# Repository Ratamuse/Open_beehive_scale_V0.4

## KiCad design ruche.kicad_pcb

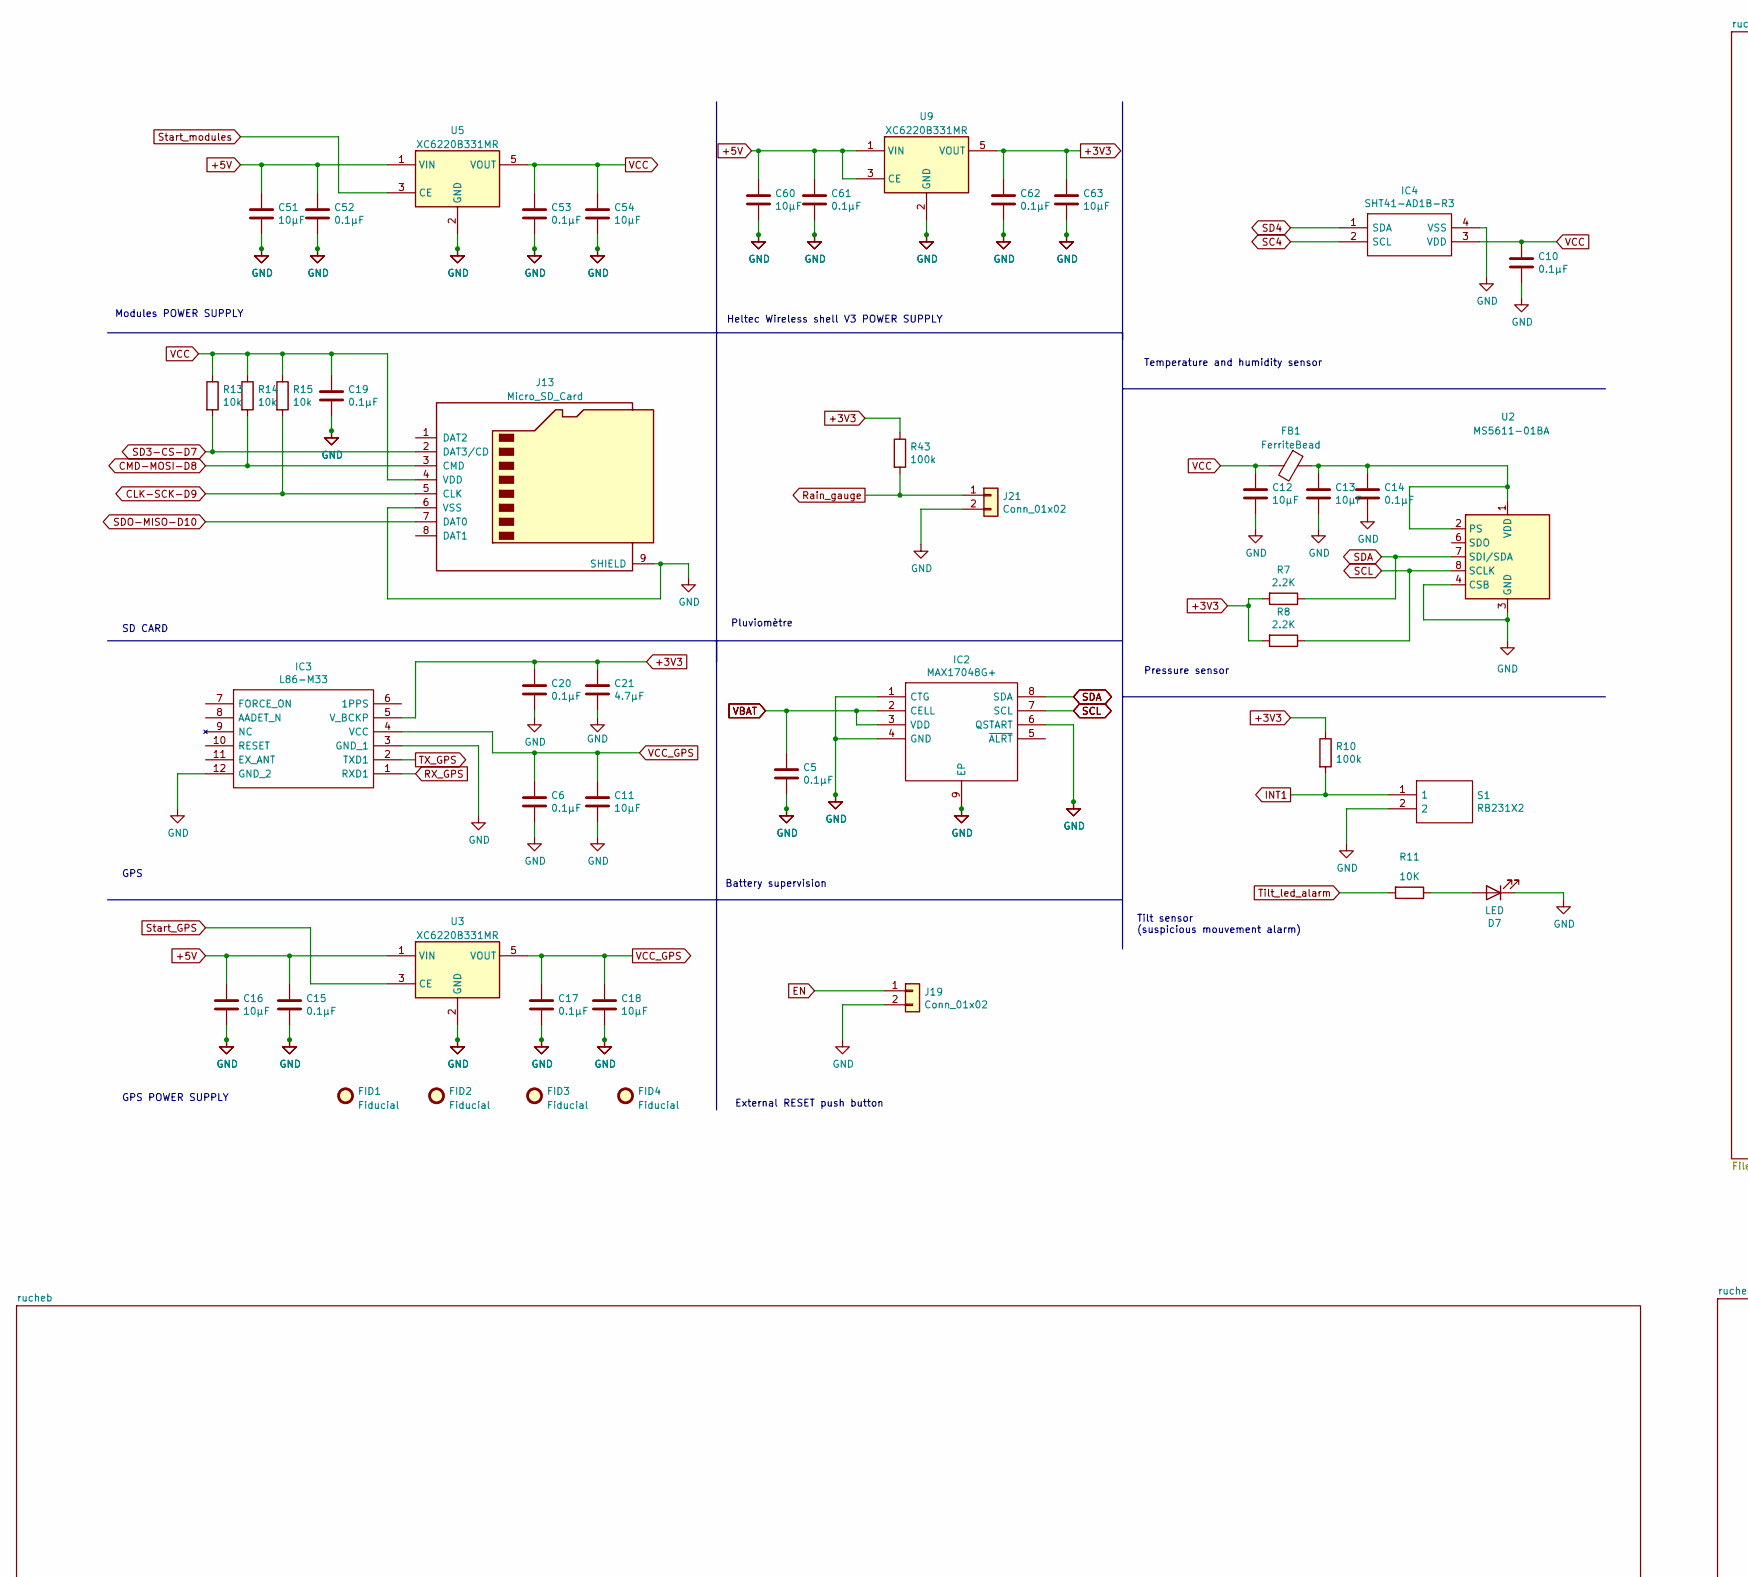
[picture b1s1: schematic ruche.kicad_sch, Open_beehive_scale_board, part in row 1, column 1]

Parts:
C5, C6, C10, C14, C17, C19, C20, C52, C53, C61, C62: 0.1µF; C_0603_1608Metric
C11, C12, C13, C18, C51, C54, C60, C63: 10µF; C_0805_2012Metric
C15: 0.1µF; C_0805_2012Metric
C16: 10µF; C_0603_1608Metric
C21: 4.7µF; C_0805_2012Metric
D7: LED; LED_0603_1608Metric
FB1: FerriteBead; R_0603_1608Metric
FID1, FID2, FID3, FID4: Fiducial; Fiducial_1mm_Mask3mm
IC2: MAX17048G+; SON50P200X200X80-9N-D; Manufacturer_Part_Number MAX17048G+; Mouser Part Number 700-MAX17048G+
IC3: L86-M33; L80-M39; Manufacturer_Part_Number L86-M33
IC4: SHT41-AD1B-R3; SHT41AD1BR3; Manufacturer_Part_Number SHT41-AD1B-R3; Mouser Part Number 403-SHT41-AD1B-R3
J13: Micro_SD_Card; microSD_HC_Hirose_DM3AT-SF-PEJM5
J19, J21: Conn_01x02; JST_PH_B2B-PH-K_1x02_P2.00mm_Vertical
R7, R8: 2.2K; R_0603_1608Metric
R10, R43: 100k; R_0603_1608Metric
R11: 10K; R_0603_1608Metric
R13, R14, R15: 10k; R_0603_1608Metric
S1: RB231X2; Manufacturer_Part_Number RB231X2; Mouser Part Number 611-RB-231X2
U2: MS5611-01BA; LGA-8_3x5mm_P1.25mm
U3, U5, U9: XC6220B331MR; SOT-23-5

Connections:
+3V3: C20.1, C21.1, C62.1, C63.1, IC3.5 (V_BCKP), R7.2, R8.2, R10.1, R43.1, U9.5 (VOUT); also elsewhere on the board
+5V: C15.1, C16.1, C51.1, C52.1, C60.1, C61.1, U3.1 (VIN), U5.1 (VIN), U9.1 (VIN), U9.3 (CE); also elsewhere on the board
CLK-SCK-D9: J13.5 (CLK), R15.2; also elsewhere on the board
CMD-MOSI-D8: J13.3 (CMD), R14.2; also elsewhere on the board
EN: J19.1; also elsewhere on the board
GND: C5.2, C6.2, C10.2, C11.2, C12.2, C13.2, C14.2, C15.2, C16.2, C17.2, C18.2, C19.2, C20.2, C21.2, C51.2, C52.2, C53.2, C54.2, C60.2, C61.2, C62.2, C63.2, D7.1 (K), IC2.1 (CTG), IC2.4 (GND), IC2.6 (QSTART), IC2.9 (EP), IC3.3 (GND_1), IC3.12 (GND_2), IC4.4 (VSS), J13.6 (VSS), J13.9 (SHIELD), J19.2, J21.2, S1.2, U2.3 (GND), U2.4 (CSB), U2.5 (CSB), U3.2 (GND), U5.2 (GND), U9.2 (GND); also elsewhere on the board
INT1: R10.2, S1.1; also elsewhere on the board
unnamed: C13.1, C14.1, FB1.1, U2.1 (VDD), U2.2 (PS)
unnamed: D7.2 (A), R11.1
RX_GPS: IC3.1 (RXD1); also elsewhere on the board
Rain_gauge: J21.1, R43.2; also elsewhere on the board
SC4: IC4.2 (SCL); also elsewhere on the board
SCL: IC2.7 (SCL), R8.1, U2.8 (SCLK); also elsewhere on the board
SD3-CS-D7: J13.2 (DAT3/CD), R13.2; also elsewhere on the board
SD4: IC4.1 (SDA); also elsewhere on the board
SDA: IC2.8 (SDA), R7.1, U2.7 (SDI/SDA); also elsewhere on the board
SDO-MISO-D10: J13.7 (DAT0); also elsewhere on the board
Start_GPS: U3.3 (CE); also elsewhere on the board
Start_modules: U5.3 (CE); also elsewhere on the board
TX_GPS: IC3.2 (TXD1); also elsewhere on the board
Tilt_led_alarm: R11.2; also elsewhere on the board
VBAT: C5.1, IC2.2 (CELL), IC2.3 (VDD); also elsewhere on the board
VCC: C10.1, C12.1, C19.1, C53.1, C54.1, FB1.2, IC4.3 (VDD), J13.4 (VDD), R13.1, R14.1, R15.1, U5.5 (VOUT); also elsewhere on the board
VCC_GPS: C6.1, C11.1, C17.1, C18.1, IC3.4 (VCC), U3.5 (VOUT)

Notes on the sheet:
SD CARD
Pluviomètre
GPS
Battery supervision
Heltec Wireless shell V3 POWER SUPPLY
Tilt sensor (suspicious mouvement alarm)
Temperature and humidity sensor
External RESET push button
Pressure sensor
Modules POWER SUPPLY
GPS POWER SUPPLY

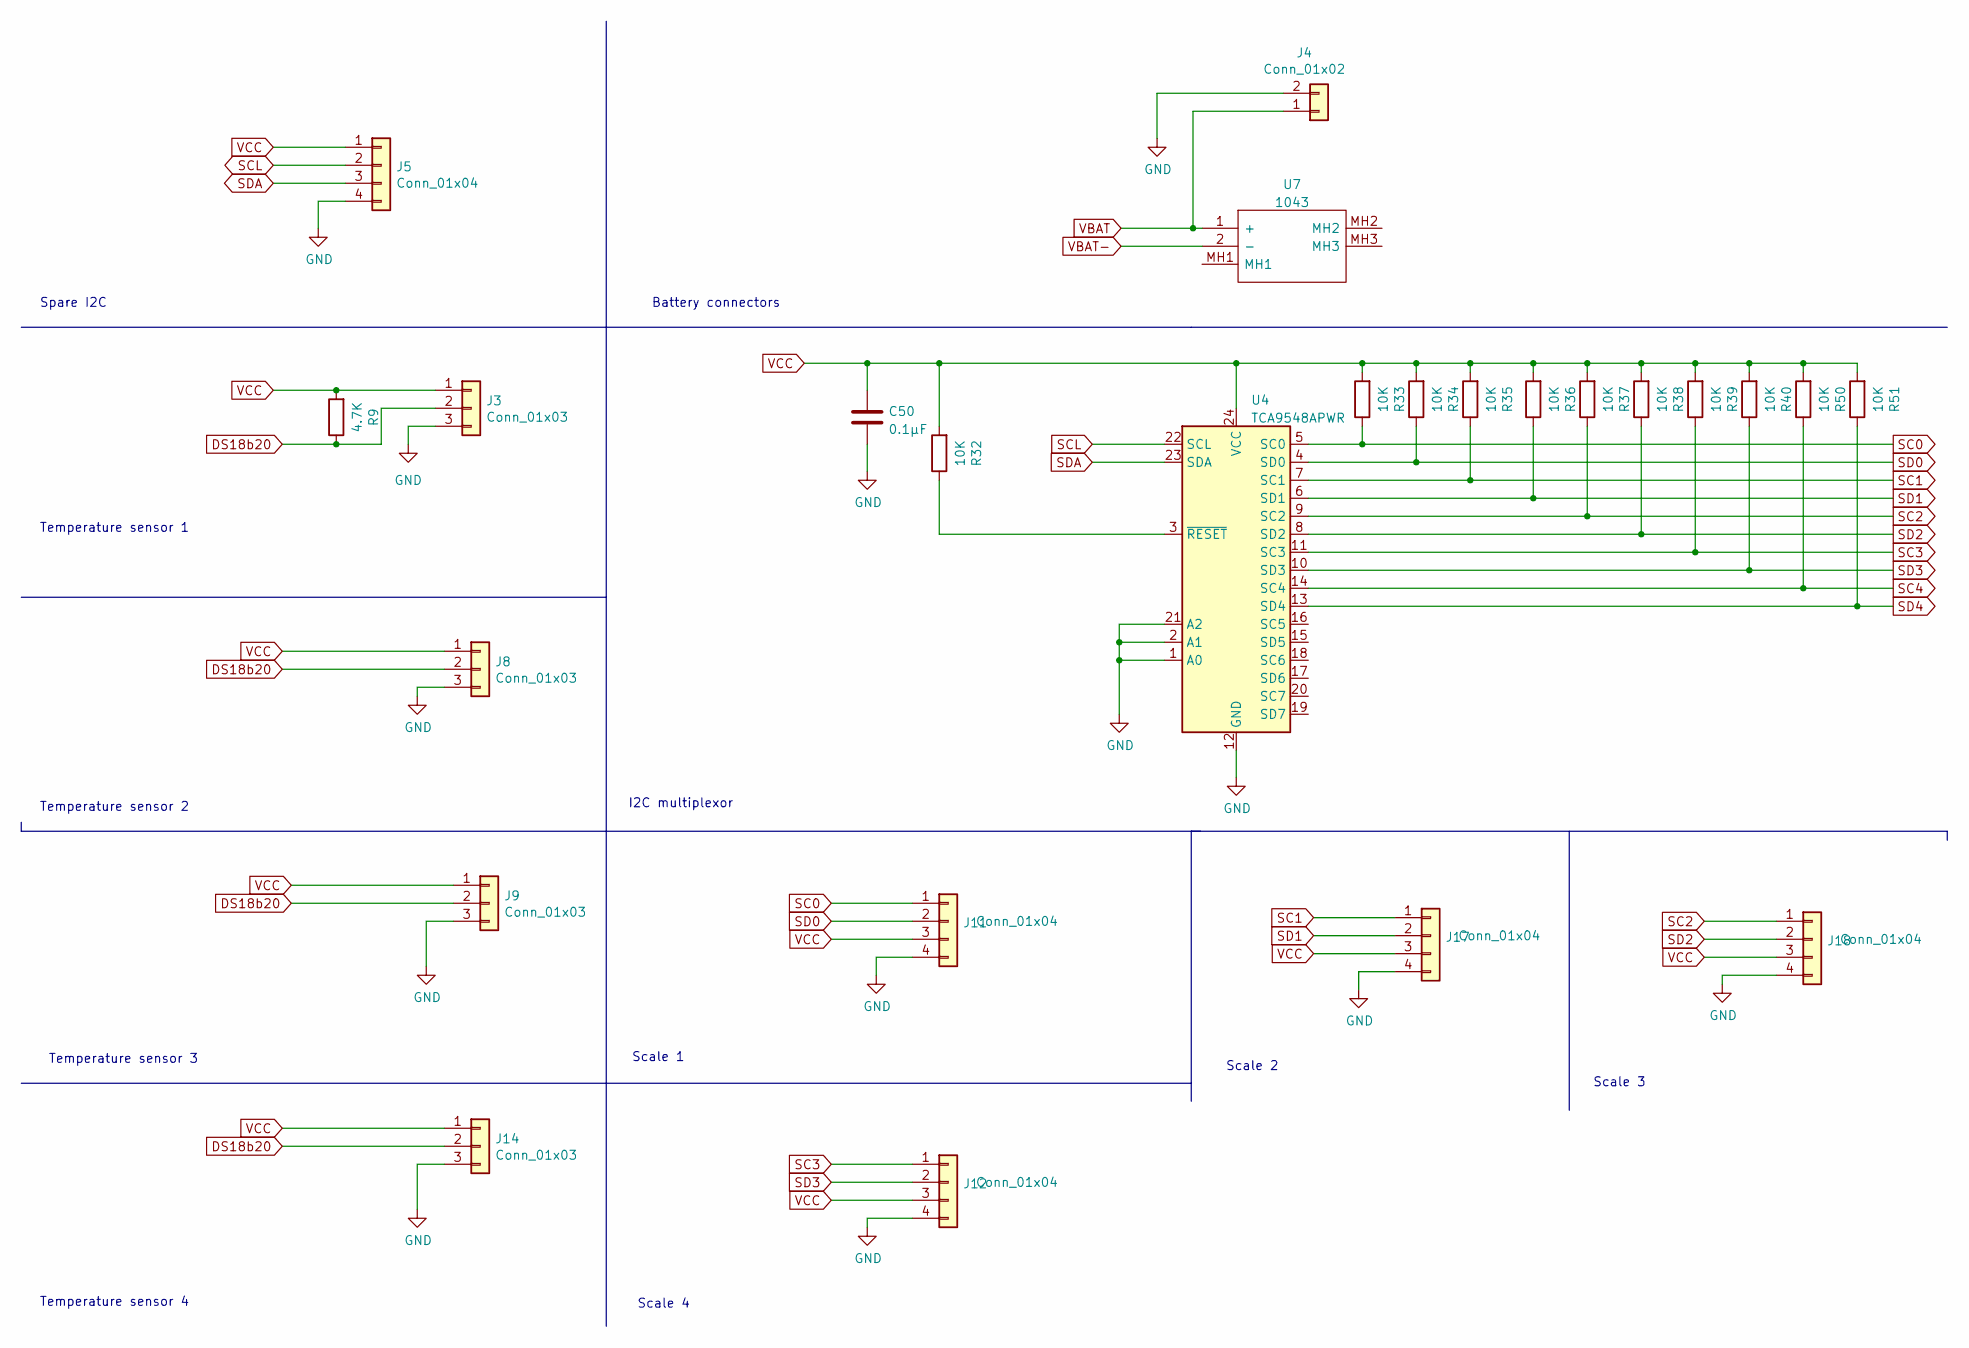
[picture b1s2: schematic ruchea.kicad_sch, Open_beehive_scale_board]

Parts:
C50: 0.1µF; C_0603_1608Metric
J3, J8, J9, J14: Conn_01x03; JST_PH_B3B-PH-K_1x03_P2.00mm_Vertical
J4: Conn_01x02; JST_PH_B2B-PH-K_1x02_P2.00mm_Vertical
J5, J11, J12, J17, J18: Conn_01x04; JST_PH_B4B-PH-K_1x04_P2.00mm_Vertical
R9: 4.7K; R_0603_1608Metric
R32, R33, R34, R35, R36, R37, R38, R39, R40, R50, R51: 10K; R_0603_1608Metric
U4: TCA9548APWR; TSSOP-24_4.4x7.8mm_P0.65mm
U7: 1043; Mouser Part Number 534-1043

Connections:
DS18b20: J3.2, J8.2, J9.2, J14.2, R9.1; also elsewhere on the board
GND: C50.2, J3.3, J4.2, J5.4, J8.3, J9.3, J11.4, J12.4, J14.3, J17.4, J18.4, U4.1 (A0), U4.2 (A1), U4.12 (GND), U4.21 (A2); also elsewhere on the board
unnamed: R32.1, U4.3 (~RESET)
SC0: J11.1, R33.1, U4.5 (SC0)
SC1: J17.1, R35.1, U4.7 (SC1)
SC2: J18.1, R37.1, U4.9 (SC2)
SC3: J12.1, R39.1, U4.11 (SC3)
SC4: R50.1, U4.14 (SC4); also elsewhere on the board
SCL: J5.2, U4.22 (SCL); also elsewhere on the board
SD0: J11.2, R34.1, U4.4 (SD0)
SD1: J17.2, R36.1, U4.6 (SD1)
SD2: J18.2, R38.1, U4.8 (SD2)
SD3: J12.2, R40.1, U4.10 (SD3)
SD4: R51.1, U4.13 (SD4); also elsewhere on the board
SDA: J5.3, U4.23 (SDA); also elsewhere on the board
VBAT: J4.1, U7.1 (+); also elsewhere on the board
VBAT-: U7.2 (-); also elsewhere on the board
VCC: C50.1, J3.1, J5.1, J8.1, J9.1, J11.3, J12.3, J14.1, J17.3, J18.3, R9.2, R32.2, R33.2, R34.2, R35.2, R36.2, R37.2, R38.2, R39.2, R40.2, R50.2, R51.2, U4.24 (VCC); also elsewhere on the board

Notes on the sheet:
Scale 4
Scale 1
Scale 3
Scale 2
I2C multiplexor
Temperature sensor 2
Battery connectors
Spare I2C
Temperature sensor 1
Temperature sensor 3
Temperature sensor 4

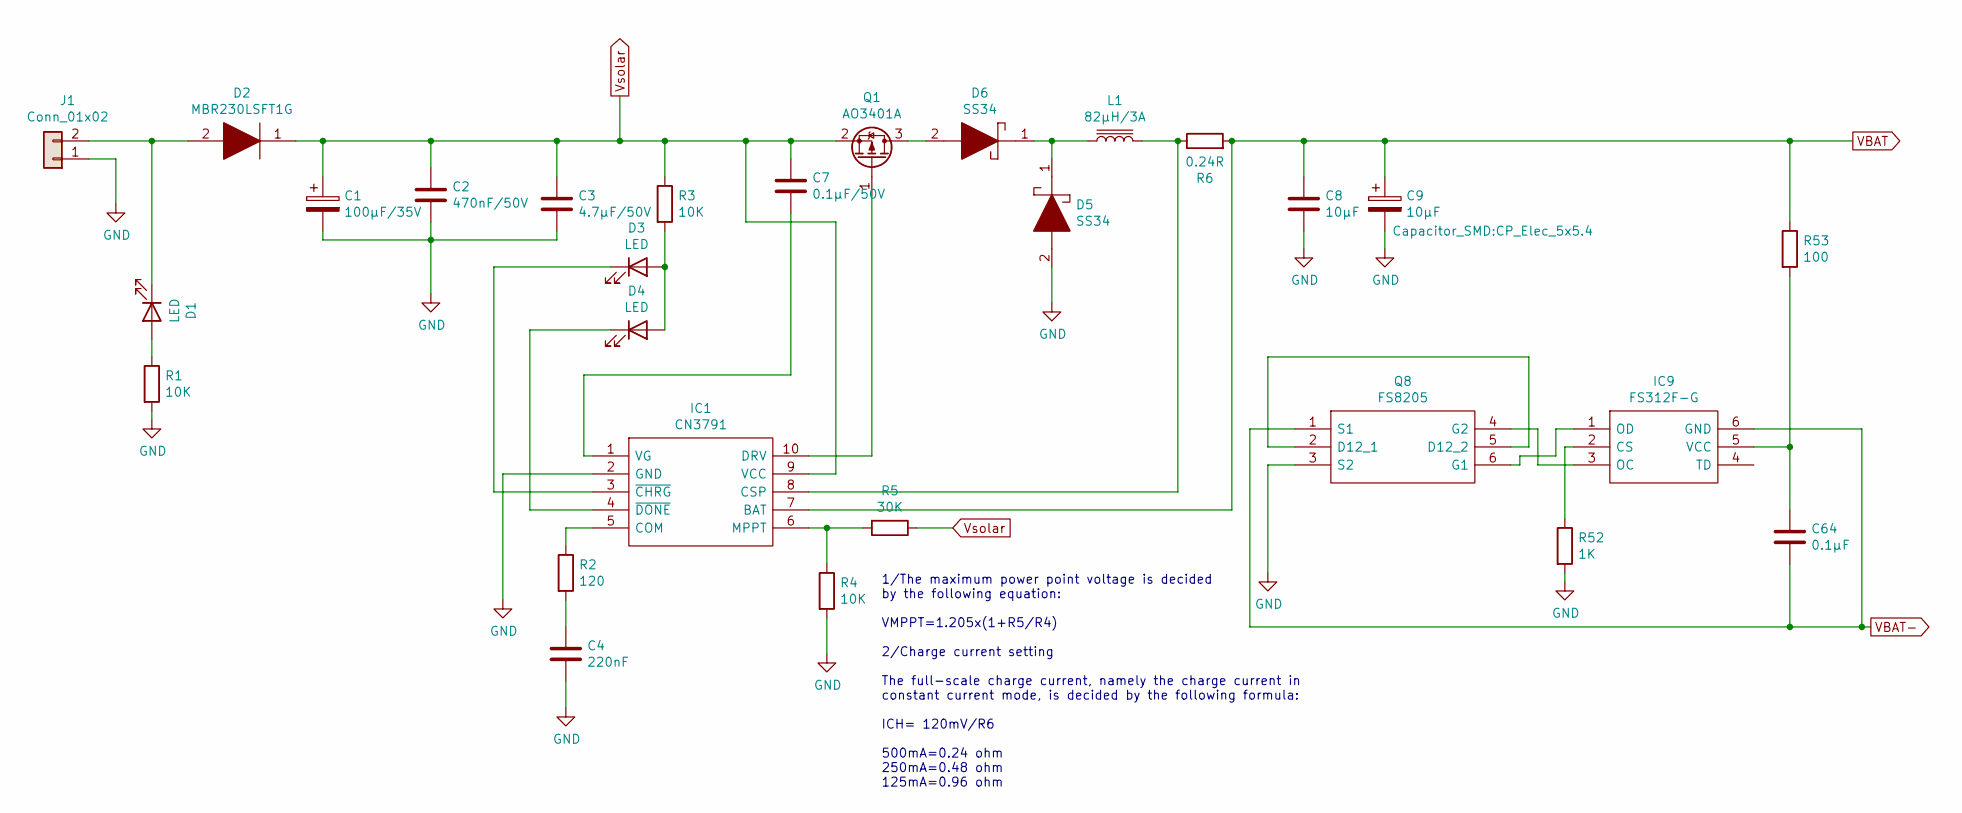
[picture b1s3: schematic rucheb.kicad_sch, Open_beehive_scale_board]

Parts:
C1: 100µF/35V; CP_Elec_6.3x7.7
C2: 470nF/50V; C_0603_1608Metric
C3: 4.7µF/50V; C_0805_2012Metric
C4: 220nF; C_0603_1608Metric
C7: 0.1µF/50V; C_0603_1608Metric
C8: 10µF; C_0805_2012Metric
C9: 10µF; CP_Elec_5x5.4
C64: 0.1µF; C_0603_1608Metric
D1, D3, D4: LED; LED_0603_1608Metric_Castellated
D2: MBR230LSFT1G; SODFL3616X98N; Manufacturer_Part_Number MBR230LSFT1G; Mouser Part Number 863-MBR230LSFT1G
D5, D6: SS34; DIOM8059X256N; Manufacturer_Part_Number SS34; Mouser Part Number 512-SS34
IC1: CN3791; SOP100P600X175-10N; Manufacturer_Part_Number CN3791
IC9: FS312F-G; SOT95P280X145-6N; Manufacturer_Part_Number FS312F-G
J1: Conn_01x02; SHDR2W90P0X500_1X2_1060X980X1380P
L1: 82µH/3A; INDPM138126X700N
Q1: AO3401A; SOT-23
Q8: FS8205; Manufacturer_Part_Number FS8205
R1, R3, R4: 10K; R_0603_1608Metric
R2: 120; R_0603_1608Metric
R5: 30K; R_0603_1608Metric
R6: 0.24R; R_2512_6332Metric
R52: 1K; R_0603_1608Metric
R53: 100; R_0603_1608Metric

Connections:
GND: C1.2, C2.2, C3.2, C4.2, C8.2, C9.2, D5.2, IC1.2 (GND), J1.1, Q8.3 (S2), R1.2, R4.2, R52.2; also elsewhere on the board
unnamed: C4.1, R2.2
unnamed: C7.2, IC1.1 (VG)
unnamed: C64.1, IC9.5 (VCC), R53.2
unnamed: D1.1 (K), D2.2, J1.2
unnamed: D1.2 (A), R1.1
unnamed: D3.1 (K), IC1.3 (~CHRG)
unnamed: D3.2 (A), D4.2 (A), R3.2
unnamed: D4.1 (K), IC1.4 (~DONE)
unnamed: D5.1, D6.1, L1.1
unnamed: D6.2, Q1.3 (D)
unnamed: IC1.5 (COM), R2.1
unnamed: IC1.6 (MPPT), R4.1, R5.2
unnamed: IC1.8 (CSP), L1.2, R6.1
unnamed: IC1.10 (DRV), Q1.1 (G)
unnamed: IC9.1 (OD), Q8.6 (G1)
unnamed: IC9.2 (CS), R52.1
unnamed: IC9.3 (OC), Q8.4 (G2)
unnamed: Q8.2 (D12_1), Q8.5 (D12_2)
VBAT: C8.1, C9.1, IC1.7 (BAT), R6.2, R53.1; also elsewhere on the board
VBAT-: C64.2, IC9.6 (GND), Q8.1 (S1); also elsewhere on the board
Vsolar: C1.1, C2.1, C3.1, C7.1, D2.1, IC1.9 (VCC), Q1.2 (S), R3.1, R5.1

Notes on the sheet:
1/The maximum power point voltage is decided by the following equation: VMPPT=1.205x(1+R5/R4) 2/Charge current setting The full-scale charge current, namely the charge current in constant current mode, is decided by the following formula: ICH= 120mV/R6 500mA=0.24 ohm 250mA=0.48 ohm 125mA=0.96 ohm

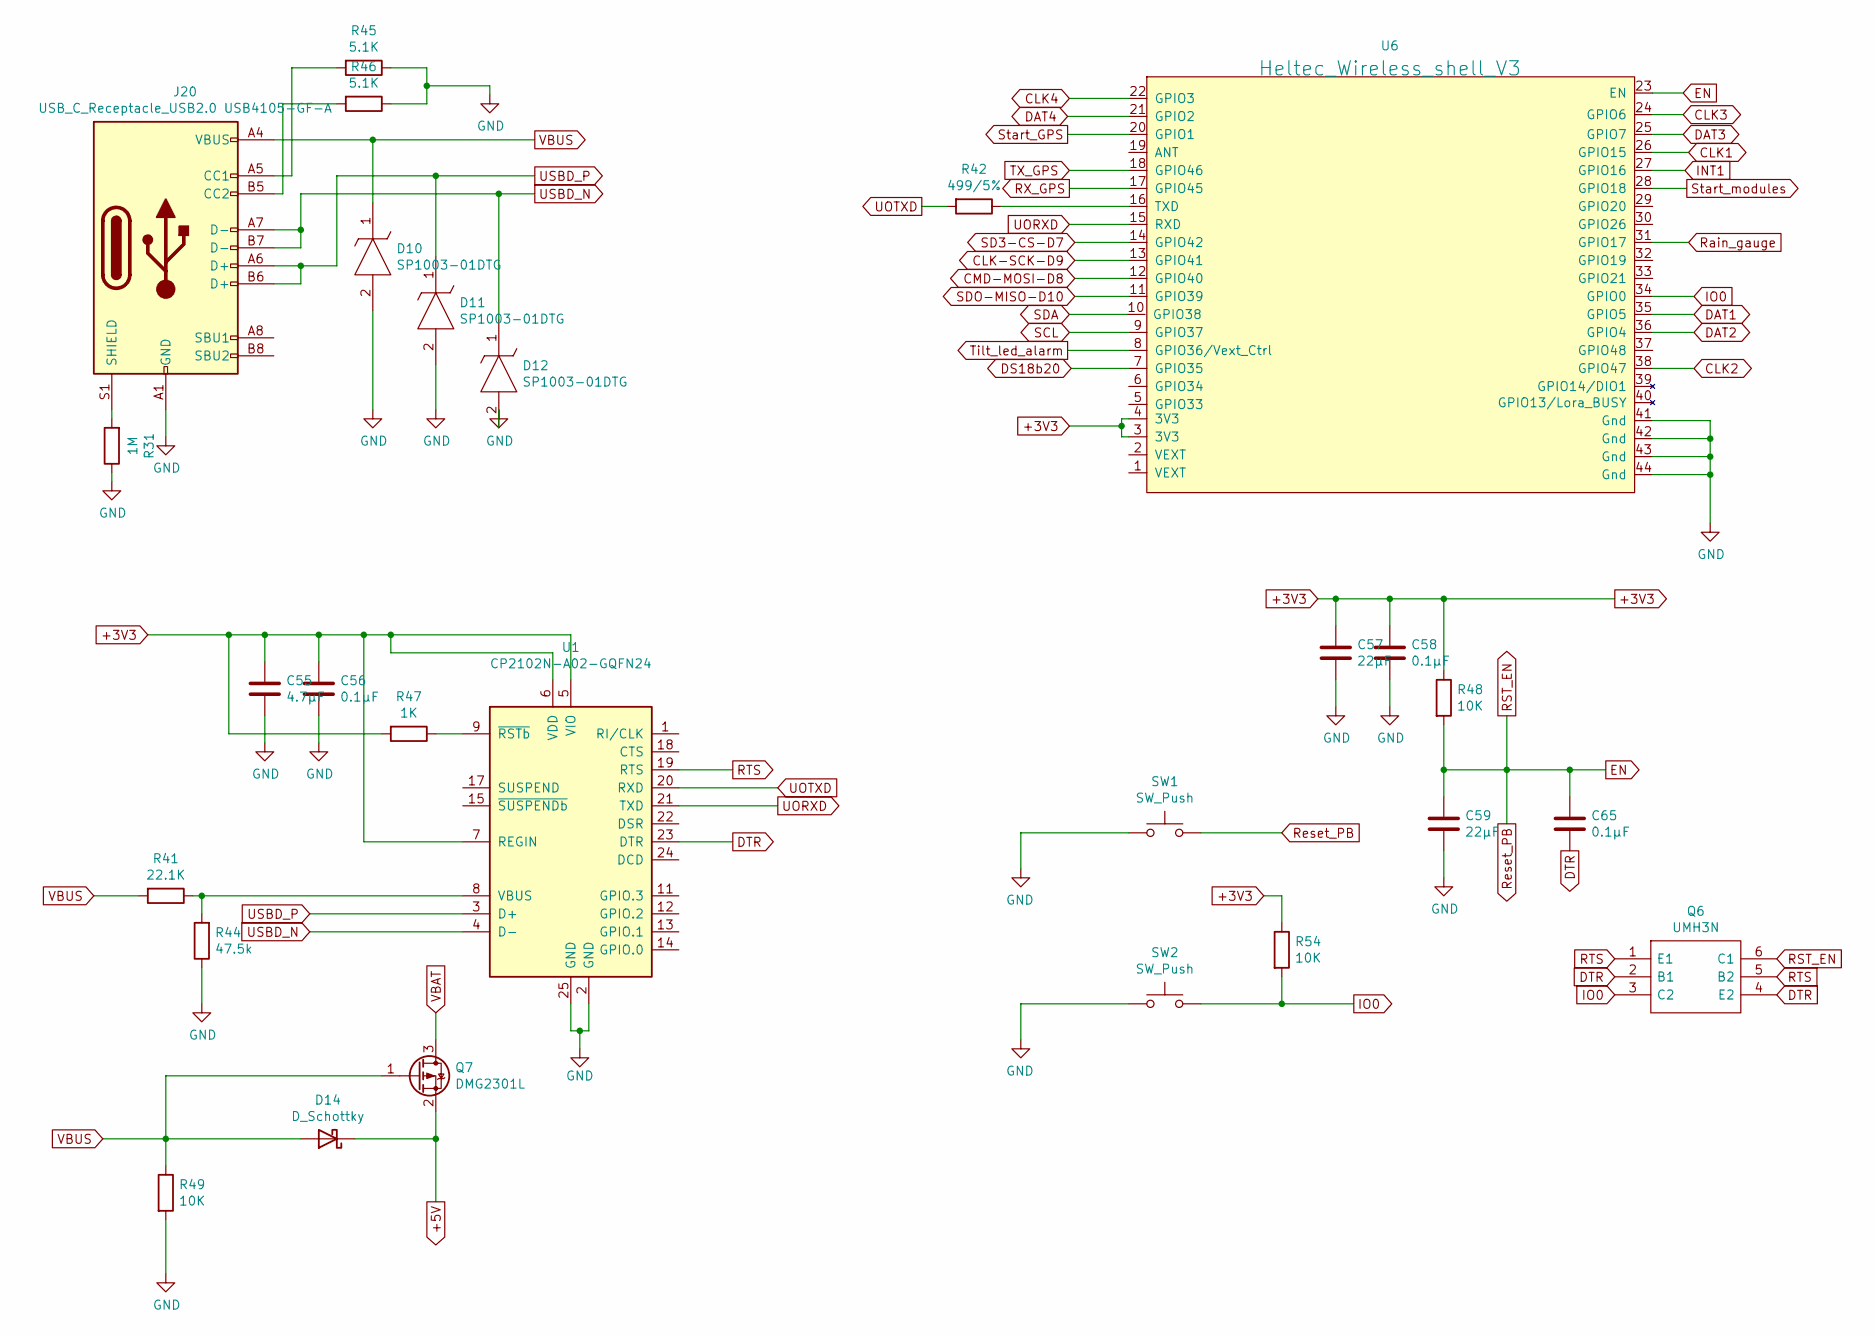
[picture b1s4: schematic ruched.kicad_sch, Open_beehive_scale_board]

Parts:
C55: 4.7µF; C_0805_2012Metric
C56, C58, C65: 0.1µF; C_0603_1608Metric
C57, C59: 22µF; C_0805_2012Metric
D10, D11, D12: SP1003-01DTG; SODFL1406X65N; Manufacturer_Part_Number SP1003-01DTG; Mouser Part Number 576-SP1003-01DTG
D14: D_Schottky; D_SOD-323
J20: USB_C_Receptacle_USB2.0 USB4105-GF-A; TYPE-C-31-M-12
Q6: UMH3N; SOT-363_SC-70-6; Manufacturer_Part_Number UMH3N
Q7: DMG2301L; SOT-23
R31: 1M; R_0603_1608Metric
R41: 22.1K; R_0603_1608Metric
R42: 499/5%; R_0603_1608Metric
R44: 47.5k; R_0603_1608Metric
R45, R46: 5.1K; R_0603_1608Metric
R47: 1K; R_0603_1608Metric
R48, R49, R54: 10K; R_0603_1608Metric
SW1, SW2: SW_Push; PTS636SL43SMTRLFS
U1: CP2102N-A02-GQFN24; QFN-24-1EP_4x4mm_P0.5mm_EP2.6x2.6mm
U6: Heltec_Wireless_shell_V3; Heltec Wireless shell V3

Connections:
+3V3: C55.1, C56.1, C57.1, C58.1, R47.2, R48.1, R54.1, U1.5 (VIO), U1.6 (VDD), U1.7 (REGIN), U6.3 (3V3), U6.4 (3V3); also elsewhere on the board
+5V: D14.1 (K), Q7.2 (S); also elsewhere on the board
CLK1: U6.26 (GPIO15); also elsewhere on the board
CLK2: U6.38 (GPIO47); also elsewhere on the board
CLK3: U6.24 (GPIO6); also elsewhere on the board
CLK4: U6.22 (GPIO3); also elsewhere on the board
CLK-SCK-D9: U6.13 (GPIO41); also elsewhere on the board
CMD-MOSI-D8: U6.12 (GPIO40); also elsewhere on the board
DAT1: U6.35 (GPIO5); also elsewhere on the board
DAT2: U6.36 (GPIO4); also elsewhere on the board
DAT3: U6.25 (GPIO7); also elsewhere on the board
DAT4: U6.21 (GPIO2); also elsewhere on the board
DS18b20: U6.7 (GPIO35); also elsewhere on the board
DTR: C65.2, Q6.2 (B1), Q6.4 (E2), U1.23 (DTR)
EN: C59.1, C65.1, Q6.6 (C1), R48.2, SW1.1, U6.23 (EN); also elsewhere on the board
GND: C55.2, C56.2, C57.2, C58.2, C59.2, D10.2, D11.2, D12.2, J20.A1 (GND), J20.A12 (GND), J20.B1 (GND), J20.B12 (GND), R31.1, R44.1, R45.1, R46.1, R49.2, SW1.2, SW2.2, U1.2 (GND), U1.25 (GND), U6.41 (Gnd), U6.42 (Gnd), U6.43 (Gnd), U6.44 (Gnd); also elsewhere on the board
INT1: U6.27 (GPIO16); also elsewhere on the board
IO0: Q6.3 (C2), R54.2, SW2.1, U6.34 (GPIO0)
unnamed: J20.A5 (CC1), R45.2
unnamed: J20.B5 (CC2), R46.2
unnamed: J20.S1 (SHIELD), R31.2
unnamed: R41.1, R44.2, U1.8 (VBUS)
unnamed: R42.1, U6.16 (TXD)
unnamed: R47.1, U1.9 (~RSTb)
RTS: Q6.1 (E1), Q6.5 (B2), U1.19 (RTS)
RX_GPS: U6.17 (GPIO45); also elsewhere on the board
Rain_gauge: U6.31 (GPIO17); also elsewhere on the board
SCL: U6.9 (GPIO37); also elsewhere on the board
SD3-CS-D7: U6.14 (GPIO42); also elsewhere on the board
SDA: U6.10 (GPIO38); also elsewhere on the board
SDO-MISO-D10: U6.11 (GPIO39); also elsewhere on the board
Start_GPS: U6.20 (GPIO1); also elsewhere on the board
Start_modules: U6.28 (GPIO18); also elsewhere on the board
TX_GPS: U6.18 (GPIO46); also elsewhere on the board
Tilt_led_alarm: U6.8 (GPIO36/Vext_Ctrl); also elsewhere on the board
UORXD: U1.21 (TXD), U6.15 (RXD)
UOTXD: R42.2, U1.20 (RXD)
USBD_N: D12.1, J20.A7 (D-), J20.B7 (D-), U1.4 (D-)
USBD_P: D11.1, J20.A6 (D+), J20.B6 (D+), U1.3 (D+)
VBAT: Q7.3 (D); also elsewhere on the board
VBUS: D10.1, D14.2 (A), J20.A4 (VBUS), J20.A9 (VBUS), J20.B4 (VBUS), J20.B9 (VBUS), Q7.1 (G), R41.2, R49.1

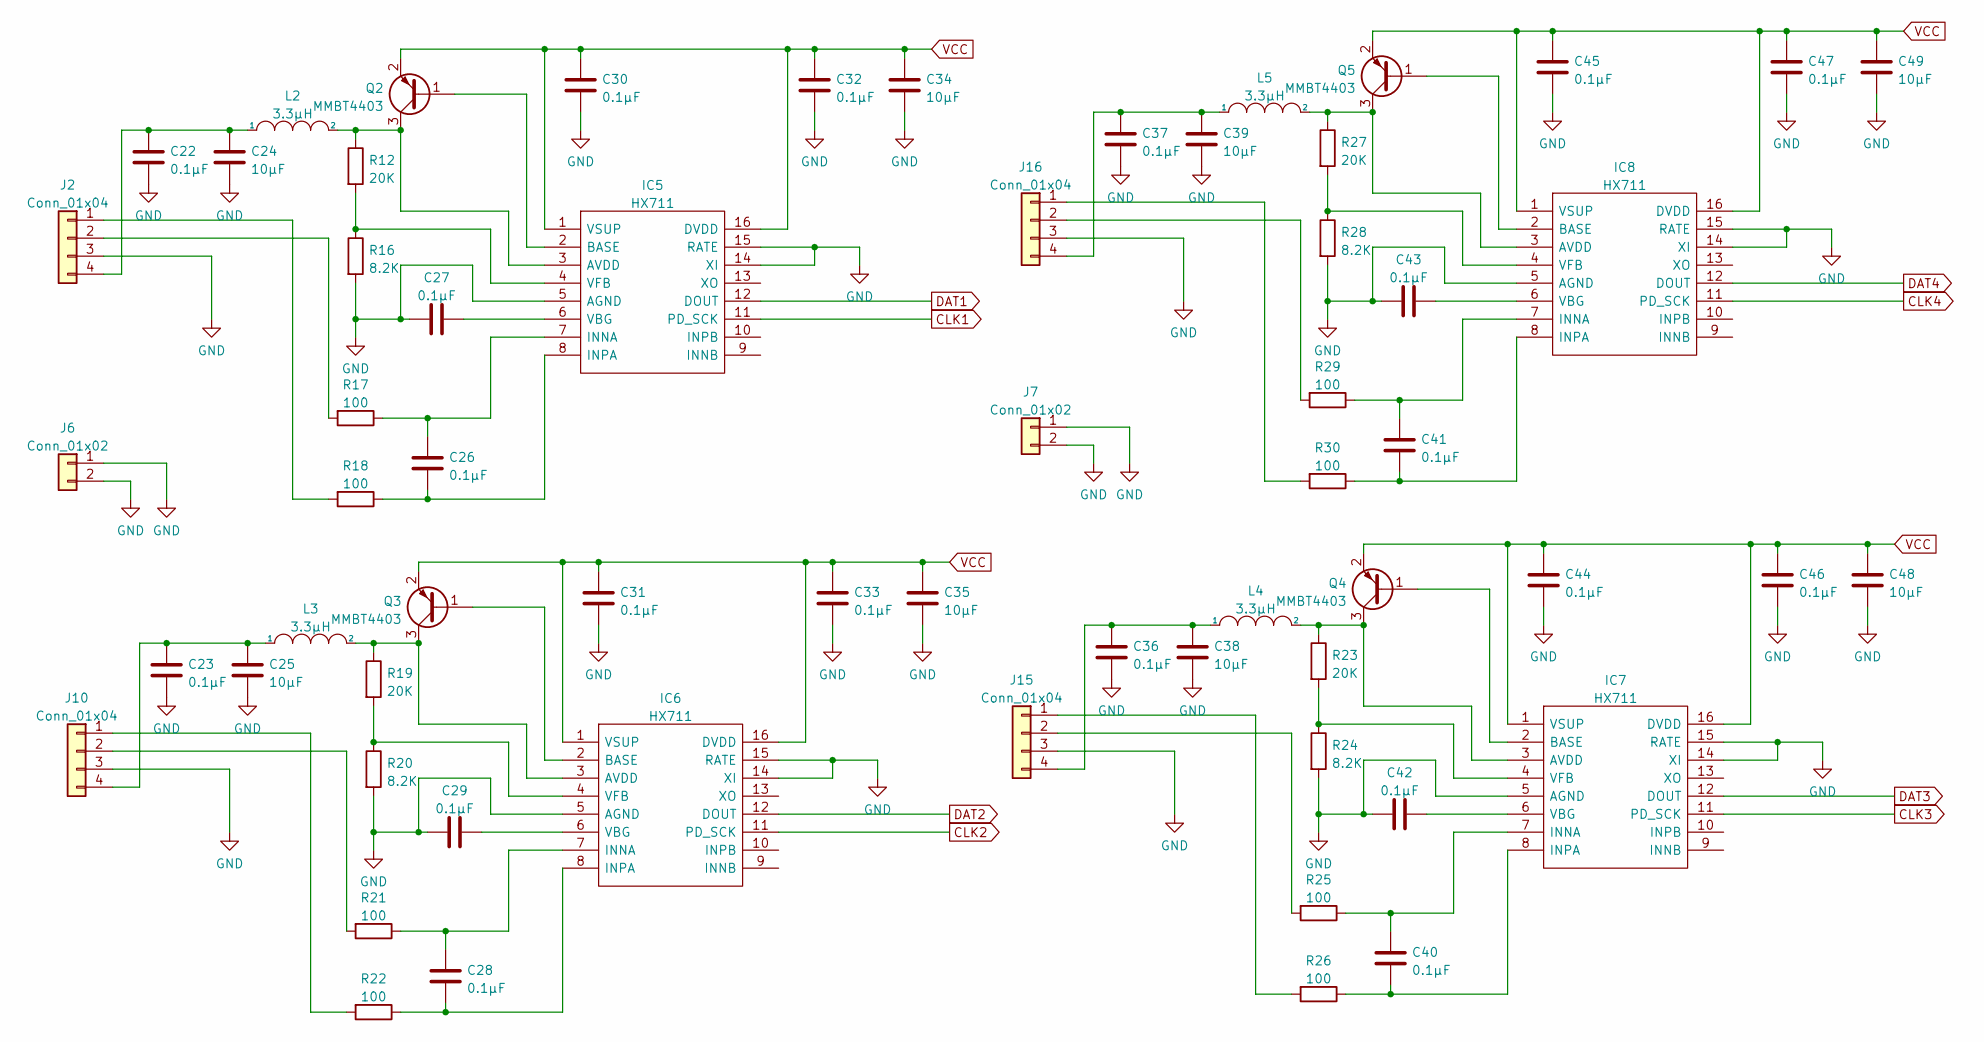
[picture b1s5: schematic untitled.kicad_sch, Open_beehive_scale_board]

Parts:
C22, C23, C26, C27, C28, C29, C30, C31, C32, C33, C36, C37, C40, C41, C42, C43, C44, C45, C46, C47: 0.1µF; C_0603_1608Metric
C24, C25, C34, C35, C38, C39, C48, C49: 10µF; C_0805_2012Metric
IC5, IC6, IC7, IC8: HX711; SOIC127P600X160-16N; Manufacturer_Part_Number HX711
J2, J10, J15, J16: Conn_01x04; 1725672
J6, J7: Conn_01x02; SHDR2W90P0X500_1X2_1060X980X1380P
L2, L3, L4, L5: 3.3µH; L_0603_1608Metric
Q2, Q3, Q4, Q5: MMBT4403; SOT-23
R12, R19, R23, R27: 20K; R_0603_1608Metric
R16, R20, R24, R28: 8.2K; R_0603_1608Metric
R17, R18, R21, R22, R25, R26, R29, R30: 100; R_0603_1608Metric

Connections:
CLK1: IC5.11 (PD_SCK); also elsewhere on the board
CLK2: IC6.11 (PD_SCK); also elsewhere on the board
CLK3: IC7.11 (PD_SCK); also elsewhere on the board
CLK4: IC8.11 (PD_SCK); also elsewhere on the board
DAT1: IC5.12 (DOUT); also elsewhere on the board
DAT2: IC6.12 (DOUT); also elsewhere on the board
DAT3: IC7.12 (DOUT); also elsewhere on the board
DAT4: IC8.12 (DOUT); also elsewhere on the board
GND: C22.2, C23.2, C24.2, C25.2, C27.1, C29.1, C30.2, C31.2, C32.2, C33.2, C34.2, C35.2, C36.2, C37.2, C38.2, C39.2, C42.1, C43.1, C44.2, C45.2, C46.2, C47.2, C48.2, C49.2, IC5.5 (AGND), IC5.14 (XI), IC5.15 (RATE), IC6.5 (AGND), IC6.14 (XI), IC6.15 (RATE), IC7.5 (AGND), IC7.14 (XI), IC7.15 (RATE), IC8.5 (AGND), IC8.14 (XI), IC8.15 (RATE), J2.3, J6.1, J6.2, J7.1, J7.2, J10.3, J15.3, J16.3, R16.2, R20.2, R24.2, R28.2; also elsewhere on the board
unnamed: C22.1, C24.1, J2.4, L2.1
unnamed: C23.1, C25.1, J10.4, L3.1
unnamed: C26.1, IC5.7 (INNA), R17.1
unnamed: C26.2, IC5.8 (INPA), R18.1
unnamed: C27.2, IC5.6 (VBG)
unnamed: C28.1, IC6.7 (INNA), R21.1
unnamed: C28.2, IC6.8 (INPA), R22.1
unnamed: C29.2, IC6.6 (VBG)
unnamed: C36.1, C38.1, J15.4, L4.1
unnamed: C37.1, C39.1, J16.4, L5.1
unnamed: C40.1, IC7.7 (INNA), R25.1
unnamed: C40.2, IC7.8 (INPA), R26.1
unnamed: C41.1, IC8.7 (INNA), R29.1
unnamed: C41.2, IC8.8 (INPA), R30.1
unnamed: C42.2, IC7.6 (VBG)
unnamed: C43.2, IC8.6 (VBG)
unnamed: IC5.2 (BASE), Q2.1 (B)
unnamed: IC5.3 (AVDD), L2.2, Q2.3 (C), R12.1
unnamed: IC5.4 (VFB), R12.2, R16.1
unnamed: IC6.2 (BASE), Q3.1 (B)
unnamed: IC6.3 (AVDD), L3.2, Q3.3 (C), R19.1
unnamed: IC6.4 (VFB), R19.2, R20.1
unnamed: IC7.2 (BASE), Q4.1 (B)
unnamed: IC7.3 (AVDD), L4.2, Q4.3 (C), R23.1
unnamed: IC7.4 (VFB), R23.2, R24.1
unnamed: IC8.2 (BASE), Q5.1 (B)
unnamed: IC8.3 (AVDD), L5.2, Q5.3 (C), R27.1
unnamed: IC8.4 (VFB), R27.2, R28.1
unnamed: J2.1, R18.2
unnamed: J2.2, R17.2
unnamed: J10.1, R22.2
unnamed: J10.2, R21.2
unnamed: J15.1, R26.2
unnamed: J15.2, R25.2
unnamed: J16.1, R30.2
unnamed: J16.2, R29.2
VCC: C30.1, C31.1, C32.1, C33.1, C34.1, C35.1, C44.1, C45.1, C46.1, C47.1, C48.1, C49.1, IC5.1 (VSUP), IC5.16 (DVDD), IC6.1 (VSUP), IC6.16 (DVDD), IC7.1 (VSUP), IC7.16 (DVDD), IC8.1 (VSUP), IC8.16 (DVDD), Q2.2 (E), Q3.2 (E), Q4.2 (E), Q5.2 (E); also elsewhere on the board

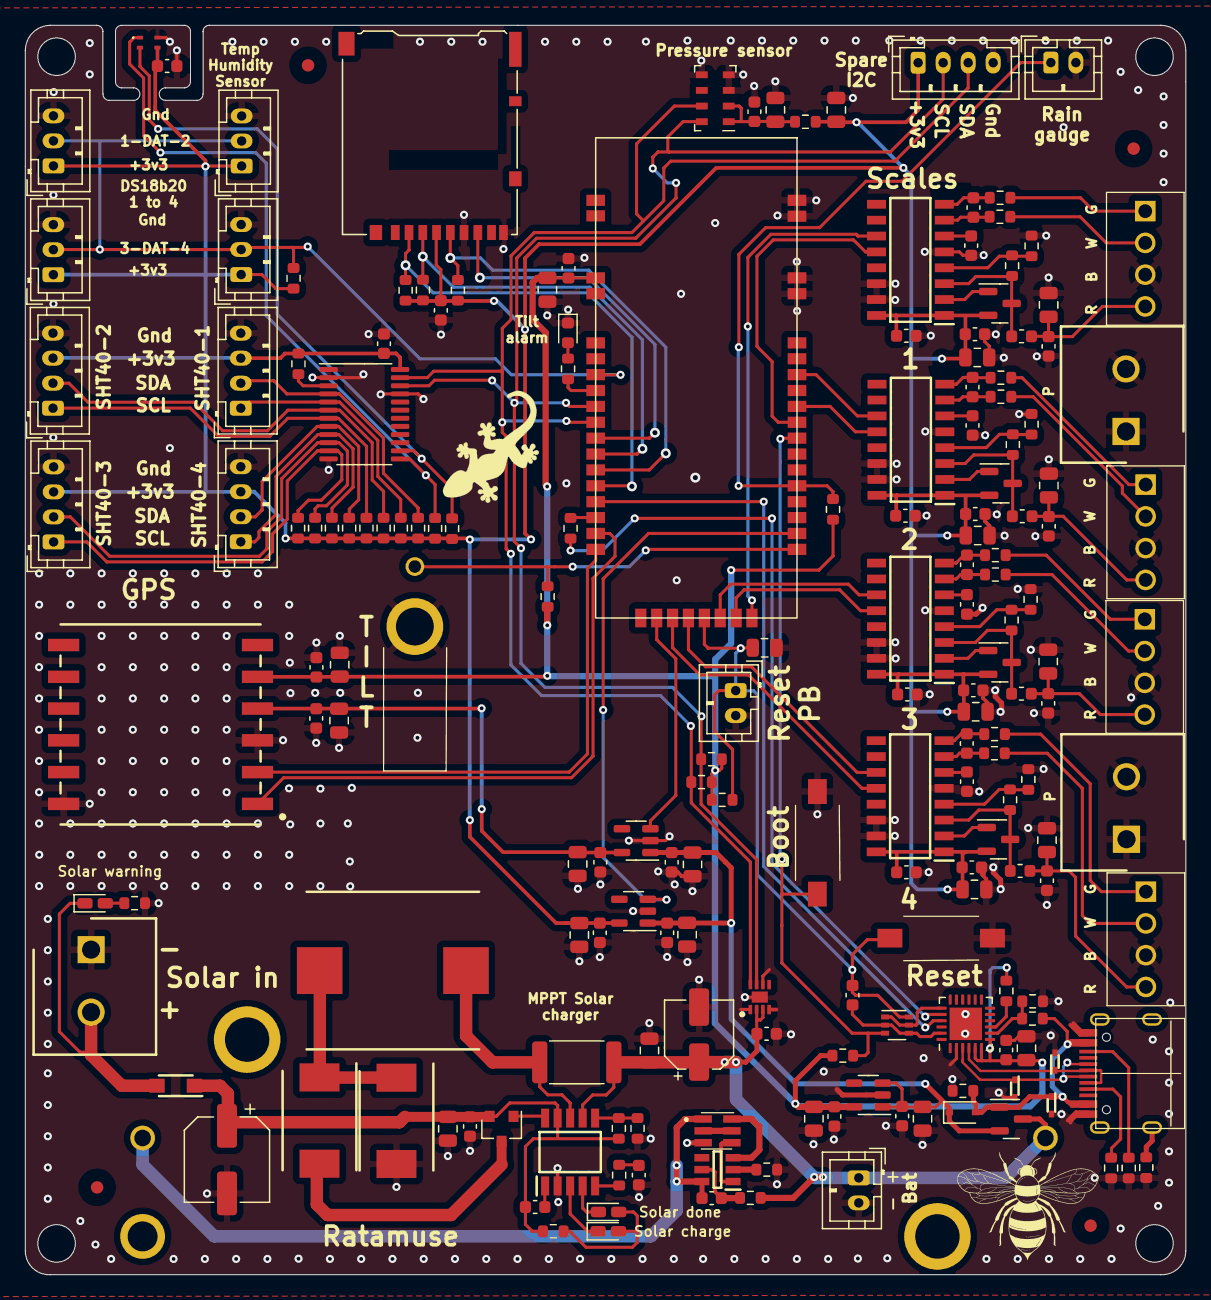
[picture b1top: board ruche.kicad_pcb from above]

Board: 2 copper layers, 92.8 x 99.9 mm, 189 parts (1 on the bottom side), 112 nets.

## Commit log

2024-03-31 Revert "update"
    This reverts commit 9afc669c055c7e8087787cb6fdf10dddd7845243.
